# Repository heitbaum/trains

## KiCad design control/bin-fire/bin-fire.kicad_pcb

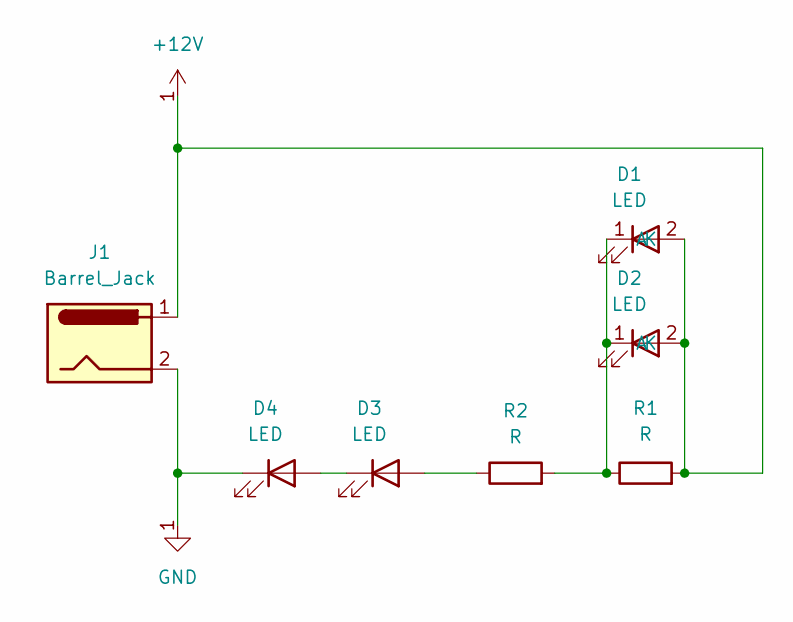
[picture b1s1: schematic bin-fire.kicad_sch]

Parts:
D1, D2, D3, D4: LED; LED_D5.0mm
J1: Barrel_Jack; BarrelJack_CUI_PJ-063AH_Horizontal_CircularHoles
R1, R2: R; R_Axial_DIN0204_L3.6mm_D1.6mm_P5.08mm_Horizontal

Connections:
+12V: D1.2 (A), D2.2 (A), J1.1, R1.2
GND: D4.1 (K), J1.2
unnamed: D1.1 (K), D2.1 (K), R1.1, R2.2
unnamed: D3.2 (A), R2.1
unnamed: D3.1 (K), D4.2 (A)

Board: 2 copper layers, 7 parts (0 on the bottom side), 5 nets, no tracks yet.

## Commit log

2025-04-12 pagoda: as printed for the train board
2025-04-12 pagoda - original
2025-08-28 bin-fire Electronic circuit and PCB design
2025-09-09 HMI updates
2025-10-18 Create DCC.md with hardware details
    Added information about EX-CSB1 and Arduino Network Shield 2.
2025-10-18 Refactor DCC.md to remove duplicates and update links
    Removed duplicate mention of Arduino Network Shield 2 and updated links.
2025-10-18 Add product links to DCC.md
    Added additional Amazon links for products related to DCC.
2025-10-18 Add more display links to DCC.md
    Added additional links for display options.
2025-10-18 Update DCC.md with new display info and link
    Added additional display resolutions and a YouTube link.
2025-10-25 Update touchscreen.md with GPIO accessory links
    Added additional links and descriptions for GPIO breakout boards and accessories for Raspberry Pi.
2025-10-25 Add new GPIO Hammer Header link to touchscreen.md
2025-10-25 Add billboard pricing information
2025-10-25 Update billboard sizes with dimensions
    Added dimensions for billboard sizes and additional details.
2025-10-25 Add height information to drive-in billboard entry
2025-11-05 Add Kato 176-8404 model and DCC details
    Added details about the Kato 176-8404 model and DCC options.
2025-11-22 Add interface details for Nextion HMI, MQTT and DCC-EX
    Added details about the interface between Nextion HMI, Mosquitto MQTT, and DCC-EX, including relevant APIs.
2025-11-22 mqtt updates
2025-12-07 mqtt
2025-12-07 dccex
2025-12-08 Add link to RFID video tutorial
2025-12-11 update subscribe to be in a thread seperate from main
2025-12-11 issue dcc-ex based on mqtt - working
2025-12-12 test publish script to turnout 14
2025-12-31 add better reconnection
2025-12-31 screen-scripts
2026-01-01 enable dcc reconnect
2026-02-05 improve config_file
2026-02-06 subscribe.service
2026-05-10 Initial
2026-05-10 v2 aspect rations
2026-05-10 v3 this one worked
2026-05-10 fuji-billbord images
2026-05-10 This is the ad play script for the radxa
2026-05-10 draft and already superceeded works
2026-05-10 version2
2026-05-10 fuji-prop-clip
2026-05-20 Add storyboard for Coca-Cola billboard animation
    Create a detailed storyboard for a vintage Coca-Cola billboard animation sequence, including style, design, animation structure, and final visual rules.
